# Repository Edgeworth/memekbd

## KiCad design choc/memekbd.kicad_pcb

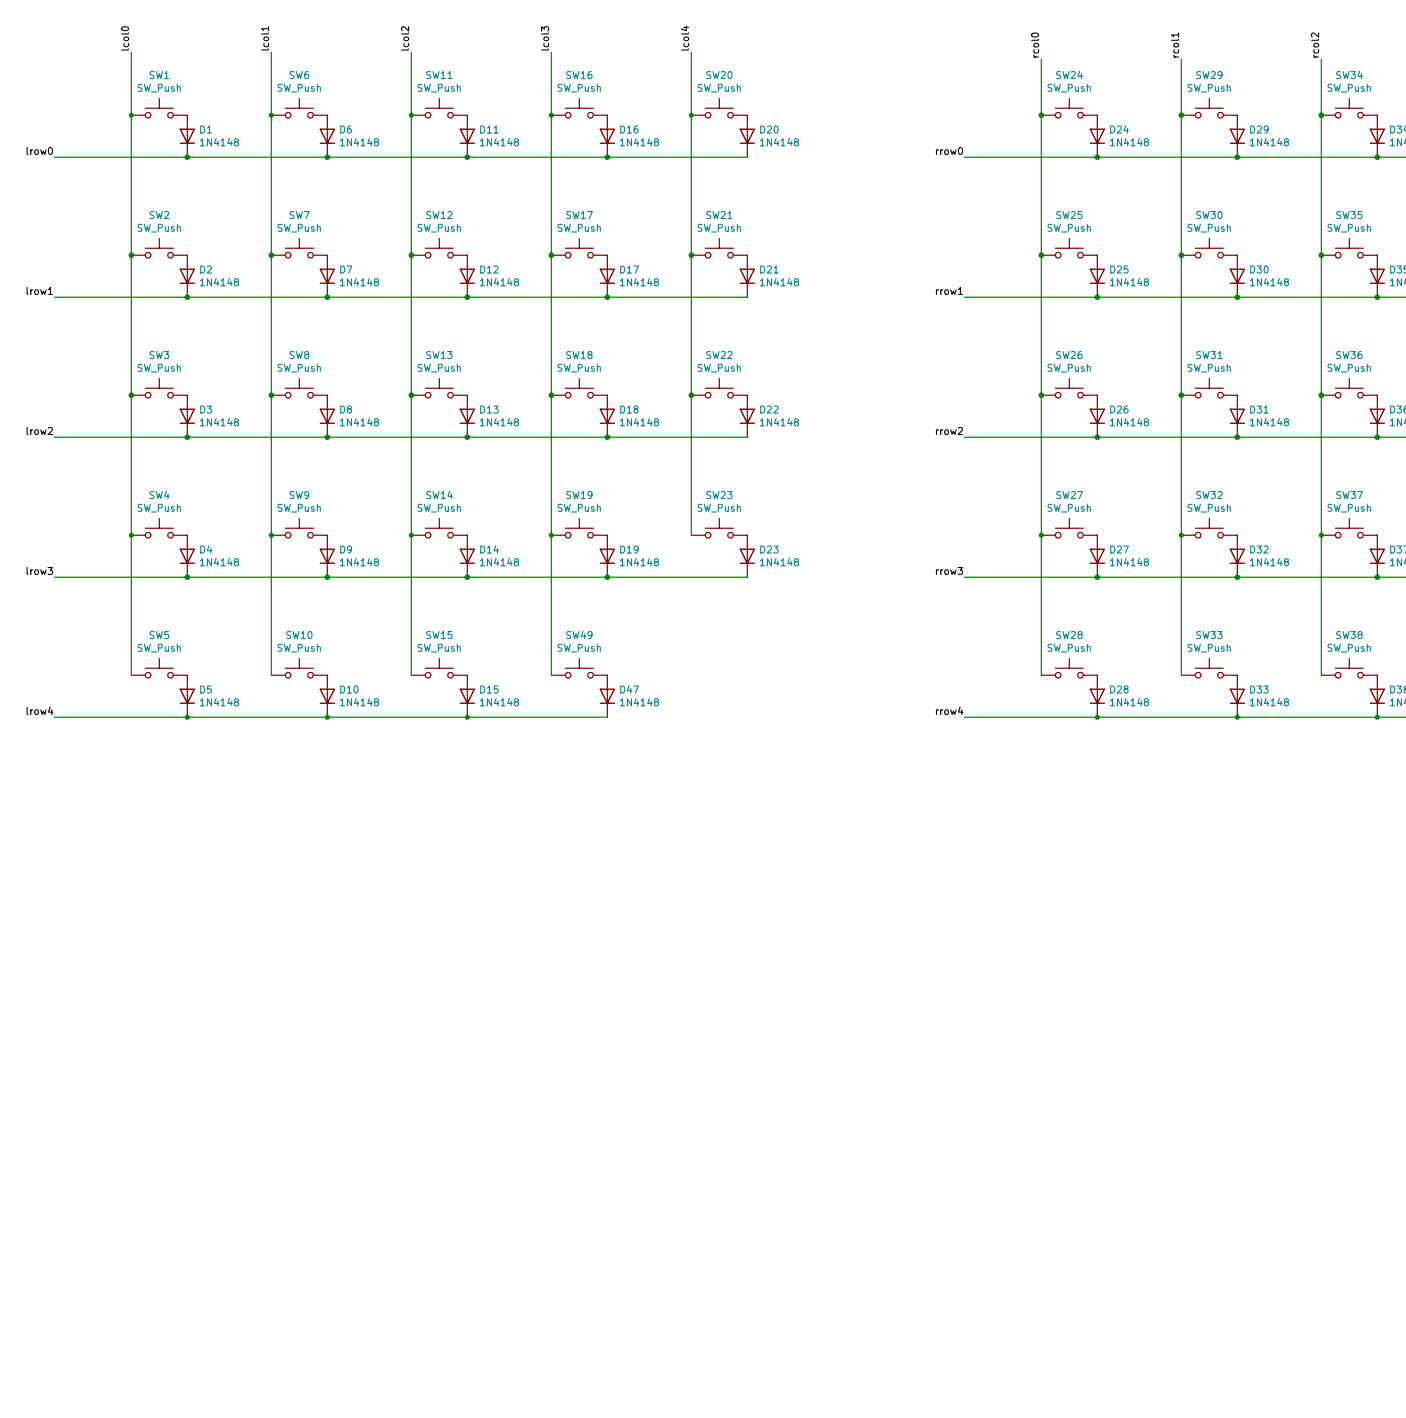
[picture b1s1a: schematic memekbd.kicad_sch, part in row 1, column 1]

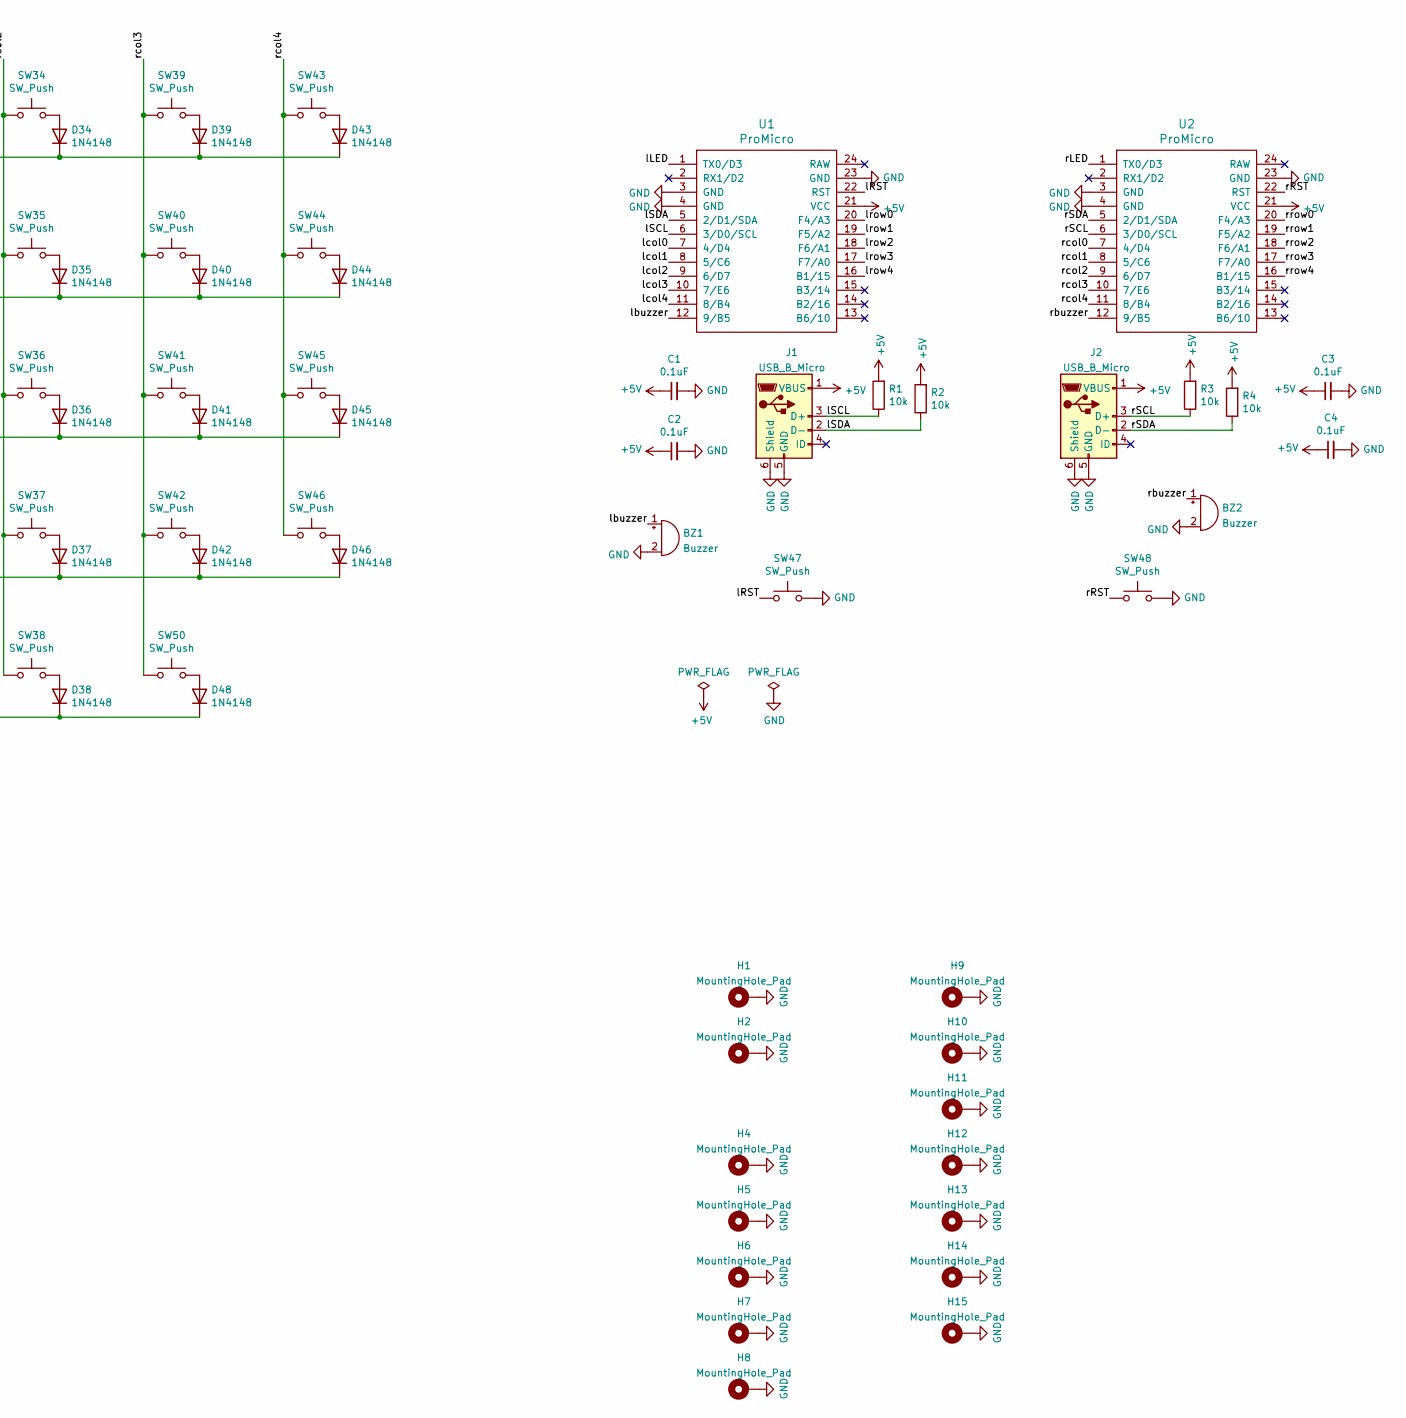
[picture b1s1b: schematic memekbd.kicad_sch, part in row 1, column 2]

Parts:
BZ1, BZ2: Buzzer; MagneticBuzzer_PUI_AT-0927-TT-6-R
C1, C2, C3, C4: 0.1uF; C_Disc_D6.0mm_W2.5mm_P5.00mm
D1, D2, D3, D4, D5, D6, D7, D8, D9, D10, D11, D12, D13, D14, D15, D16, D17, D18, D19, D20, D21, D22, D23, D24, D25, D26, D27, D28, D29, D30, D31, D32, D33, D34, D35, D36, D37, D38, D39, D40, D41, D42, D43, D44, D45, D46, D47, D48: 1N4148; D_DO-35_SOD27_P7.62mm_Horizontal
H1, H2, H4, H5, H6, H7, H8, H9, H10, H11, H12, H13, H14, H15: MountingHole_Pad; MountingHole_3.2mm_M3_ISO7380_Pad
J1, J2: USB_B_Micro; USB_Micro-B_Wuerth_629105150521
R1, R2, R3, R4: 10k; R_Axial_DIN0207_L6.3mm_D2.5mm_P7.62mm_Horizontal
SW1, SW2, SW3, SW4, SW5, SW6, SW7, SW8, SW9, SW10, SW11, SW12, SW13, SW14, SW15, SW16, SW17, SW18, SW19, SW20, SW21, SW22, SW23, SW24, SW25, SW26, SW27, SW28, SW29, SW30, SW31, SW32, SW33, SW34, SW35, SW36, SW37, SW38, SW39, SW40, SW41, SW42, SW43, SW44, SW45, SW46, SW49, SW50: SW_Push; ChocV1_Hotswap
SW47, SW48: SW_Push; SW_PUSH_6mm_H7.3mm
U1, U2: ProMicro; ProMicro_v3.5

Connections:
+5V: C1.1, C2.1, C3.1, C4.1, J1.1 (VBUS), J2.1 (VBUS), R1.2, R2.2, R3.2, R4.2, U1.21 (VCC), U2.21 (VCC)
/lLED: U1.1 (TX0/D3)
/lRST: SW47.1, U1.22 (RST)
/lSCL: J1.3 (D+), R1.1, U1.6 (3/D0/SCL)
/lSDA: J1.2 (D-), R2.1, U1.5 (2/D1/SDA)
/lbuzzer: BZ1.1 (-), U1.12 (9/B5)
/lcol0: SW1.1, SW2.1, SW3.1, SW4.1, SW5.1, U1.7 (4/D4)
/lcol1: SW6.1, SW7.1, SW8.1, SW9.1, SW10.1, U1.8 (5/C6)
/lcol2: SW11.1, SW12.1, SW13.1, SW14.1, SW15.1, U1.9 (6/D7)
/lcol3: SW16.1, SW17.1, SW18.1, SW19.1, SW49.1, U1.10 (7/E6)
/lcol4: SW20.1, SW21.1, SW22.1, SW23.1, U1.11 (8/B4)
/lrow0: D1.1 (K), D6.1 (K), D11.1 (K), D16.1 (K), D20.1 (K), U1.20 (F4/A3)
/lrow1: D2.1 (K), D7.1 (K), D12.1 (K), D17.1 (K), D21.1 (K), U1.19 (F5/A2)
/lrow2: D3.1 (K), D8.1 (K), D13.1 (K), D18.1 (K), D22.1 (K), U1.18 (F6/A1)
/lrow3: D4.1 (K), D9.1 (K), D14.1 (K), D19.1 (K), D23.1 (K), U1.17 (F7/A0)
/lrow4: D5.1 (K), D10.1 (K), D15.1 (K), D47.1 (K), U1.16 (B1/15)
/rLED: U2.1 (TX0/D3)
/rRST: SW48.1, U2.22 (RST)
/rSCL: J2.3 (D+), R3.1, U2.6 (3/D0/SCL)
/rSDA: J2.2 (D-), R4.1, U2.5 (2/D1/SDA)
/rbuzzer: BZ2.1 (-), U2.12 (9/B5)
/rcol0: SW24.1, SW25.1, SW26.1, SW27.1, SW28.1, U2.7 (4/D4)
/rcol1: SW29.1, SW30.1, SW31.1, SW32.1, SW33.1, U2.8 (5/C6)
/rcol2: SW34.1, SW35.1, SW36.1, SW37.1, SW38.1, U2.9 (6/D7)
/rcol3: SW39.1, SW40.1, SW41.1, SW42.1, SW50.1, U2.10 (7/E6)
/rcol4: SW43.1, SW44.1, SW45.1, SW46.1, U2.11 (8/B4)
/rrow0: D24.1 (K), D29.1 (K), D34.1 (K), D39.1 (K), D43.1 (K), U2.20 (F4/A3)
/rrow1: D25.1 (K), D30.1 (K), D35.1 (K), D40.1 (K), D44.1 (K), U2.19 (F5/A2)
/rrow2: D26.1 (K), D31.1 (K), D36.1 (K), D41.1 (K), D45.1 (K), U2.18 (F6/A1)
/rrow3: D27.1 (K), D32.1 (K), D37.1 (K), D42.1 (K), D46.1 (K), U2.17 (F7/A0)
/rrow4: D28.1 (K), D33.1 (K), D38.1 (K), D48.1 (K), U2.16 (B1/15)
GND: BZ1.2 (+), BZ2.2 (+), C1.2, C2.2, C3.2, C4.2, H1.1, H2.1, H4.1, H5.1, H6.1, H7.1, H8.1, H9.1, H10.1, H11.1, H12.1, H13.1, H14.1, H15.1, J1.5 (GND), J1.6 (Shield), J2.5 (GND), J2.6 (Shield), SW47.2, SW48.2, U1.3 (GND), U1.4 (GND), U1.23 (GND), U2.3 (GND), U2.4 (GND), U2.23 (GND)
unnamed: D1.2 (A), SW1.2
unnamed: D2.2 (A), SW2.2
unnamed: D3.2 (A), SW3.2
unnamed: D4.2 (A), SW4.2
unnamed: D5.2 (A), SW5.2
unnamed: D6.2 (A), SW6.2
unnamed: D7.2 (A), SW7.2
unnamed: D8.2 (A), SW8.2
unnamed: D9.2 (A), SW9.2
unnamed: D10.2 (A), SW10.2
unnamed: D11.2 (A), SW11.2
unnamed: D12.2 (A), SW12.2
unnamed: D13.2 (A), SW13.2
unnamed: D14.2 (A), SW14.2
unnamed: D15.2 (A), SW15.2
unnamed: D16.2 (A), SW16.2
unnamed: D17.2 (A), SW17.2
unnamed: D18.2 (A), SW18.2
unnamed: D19.2 (A), SW19.2
unnamed: D20.2 (A), SW20.2
unnamed: D21.2 (A), SW21.2
unnamed: D22.2 (A), SW22.2
unnamed: D23.2 (A), SW23.2
unnamed: D24.2 (A), SW24.2
unnamed: D25.2 (A), SW25.2
unnamed: D26.2 (A), SW26.2
unnamed: D27.2 (A), SW27.2
unnamed: D28.2 (A), SW28.2
unnamed: D29.2 (A), SW29.2
unnamed: D30.2 (A), SW30.2
unnamed: D31.2 (A), SW31.2
unnamed: D32.2 (A), SW32.2
unnamed: D33.2 (A), SW33.2
unnamed: D34.2 (A), SW34.2
unnamed: D35.2 (A), SW35.2
unnamed: D36.2 (A), SW36.2
unnamed: D37.2 (A), SW37.2
unnamed: D38.2 (A), SW38.2
unnamed: D39.2 (A), SW39.2
unnamed: D40.2 (A), SW40.2
unnamed: D41.2 (A), SW41.2
unnamed: D42.2 (A), SW42.2
unnamed: D43.2 (A), SW43.2
unnamed: D44.2 (A), SW44.2
unnamed: D45.2 (A), SW45.2
unnamed: D46.2 (A), SW46.2
unnamed: D47.2 (A), SW49.2
unnamed: D48.2 (A), SW50.2

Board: 2 copper layers, 126 parts (4 on the bottom side), 78 nets, no tracks yet.

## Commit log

2021-06-06 Initial commit.
2021-06-06 Add foostan's kicad libraries. Finish design of schematic, passes ERC
2021-06-06 Assign footprints.
2021-06-06 Most of pcb layout work.
2021-06-07 More pcb layout.
2021-06-07 Finish layout
2021-06-07 Stagger
2021-06-07 Thumb position
2021-06-08 Fix up thumb positions.
2021-06-08 Finish key positions.
2021-06-08 Start edge cuts.
2021-06-08 Rounded corners.
2021-06-09 Remove unnecessary packages. Refactor directory structure.
2021-06-09 Remove unnecessary libraries. Update footprints
2021-06-09 Add mounting holes.
2021-06-09 Some routing
2021-06-09 Some LED changes.
2021-06-09 Routing progress
2021-06-09 Create only mounting hole, edge, and tracks portion
2021-06-11 Mounting holes in schematic.
2021-06-26 Pcb progress
2021-06-26 Finish routing
2021-06-26 Add flipped bottom plate
2021-06-26 Progress on top plate
2021-06-26 Done
2021-06-26 Add left
2021-06-26 Add other subparts
2021-06-26 Fix bug...
2021-06-26 Fix refs
2021-06-26 Update pcb
2021-06-26 Update subpcbs
2021-06-27 Re-finish manual layout
2021-08-22 Fix top plate wrong edge cuts.
2021-08-23 Fix bug with no connection to leds on right side.
2021-08-28 Change schematic to use micro usb
2021-09-27 Update mounting hole footprint
2021-09-27 Rotate all key switches.
2021-09-27 Change location of keys.
2021-09-27 Work on reorg of keys
2021-10-03 quantise
2021-10-04 place holes
2021-10-12 finish
2021-10-18 update board rules
2021-10-26 reorganise
2021-10-26 add choc footprint
2021-10-28 update footprint
2021-10-28 work on choc version
2021-10-29 add mounting holes
2021-10-29 fix diodes not having vertical space in choc
2021-10-29 progress
2021-10-30 progress on plates
2021-10-30 add routed left board
2021-10-30 add routed right board
2021-11-03 remove leds from choc
2021-11-30 add buzzer to schematic
2021-11-30 add buzzer to pcb
2021-11-30 add dsns
2021-11-30 import left ses
2021-11-30 fix left
2021-11-30 import right ses
2021-11-30 fix right
2021-12-04 add gerbers
2021-12-27 update location of resistors. fix bug in top plate
